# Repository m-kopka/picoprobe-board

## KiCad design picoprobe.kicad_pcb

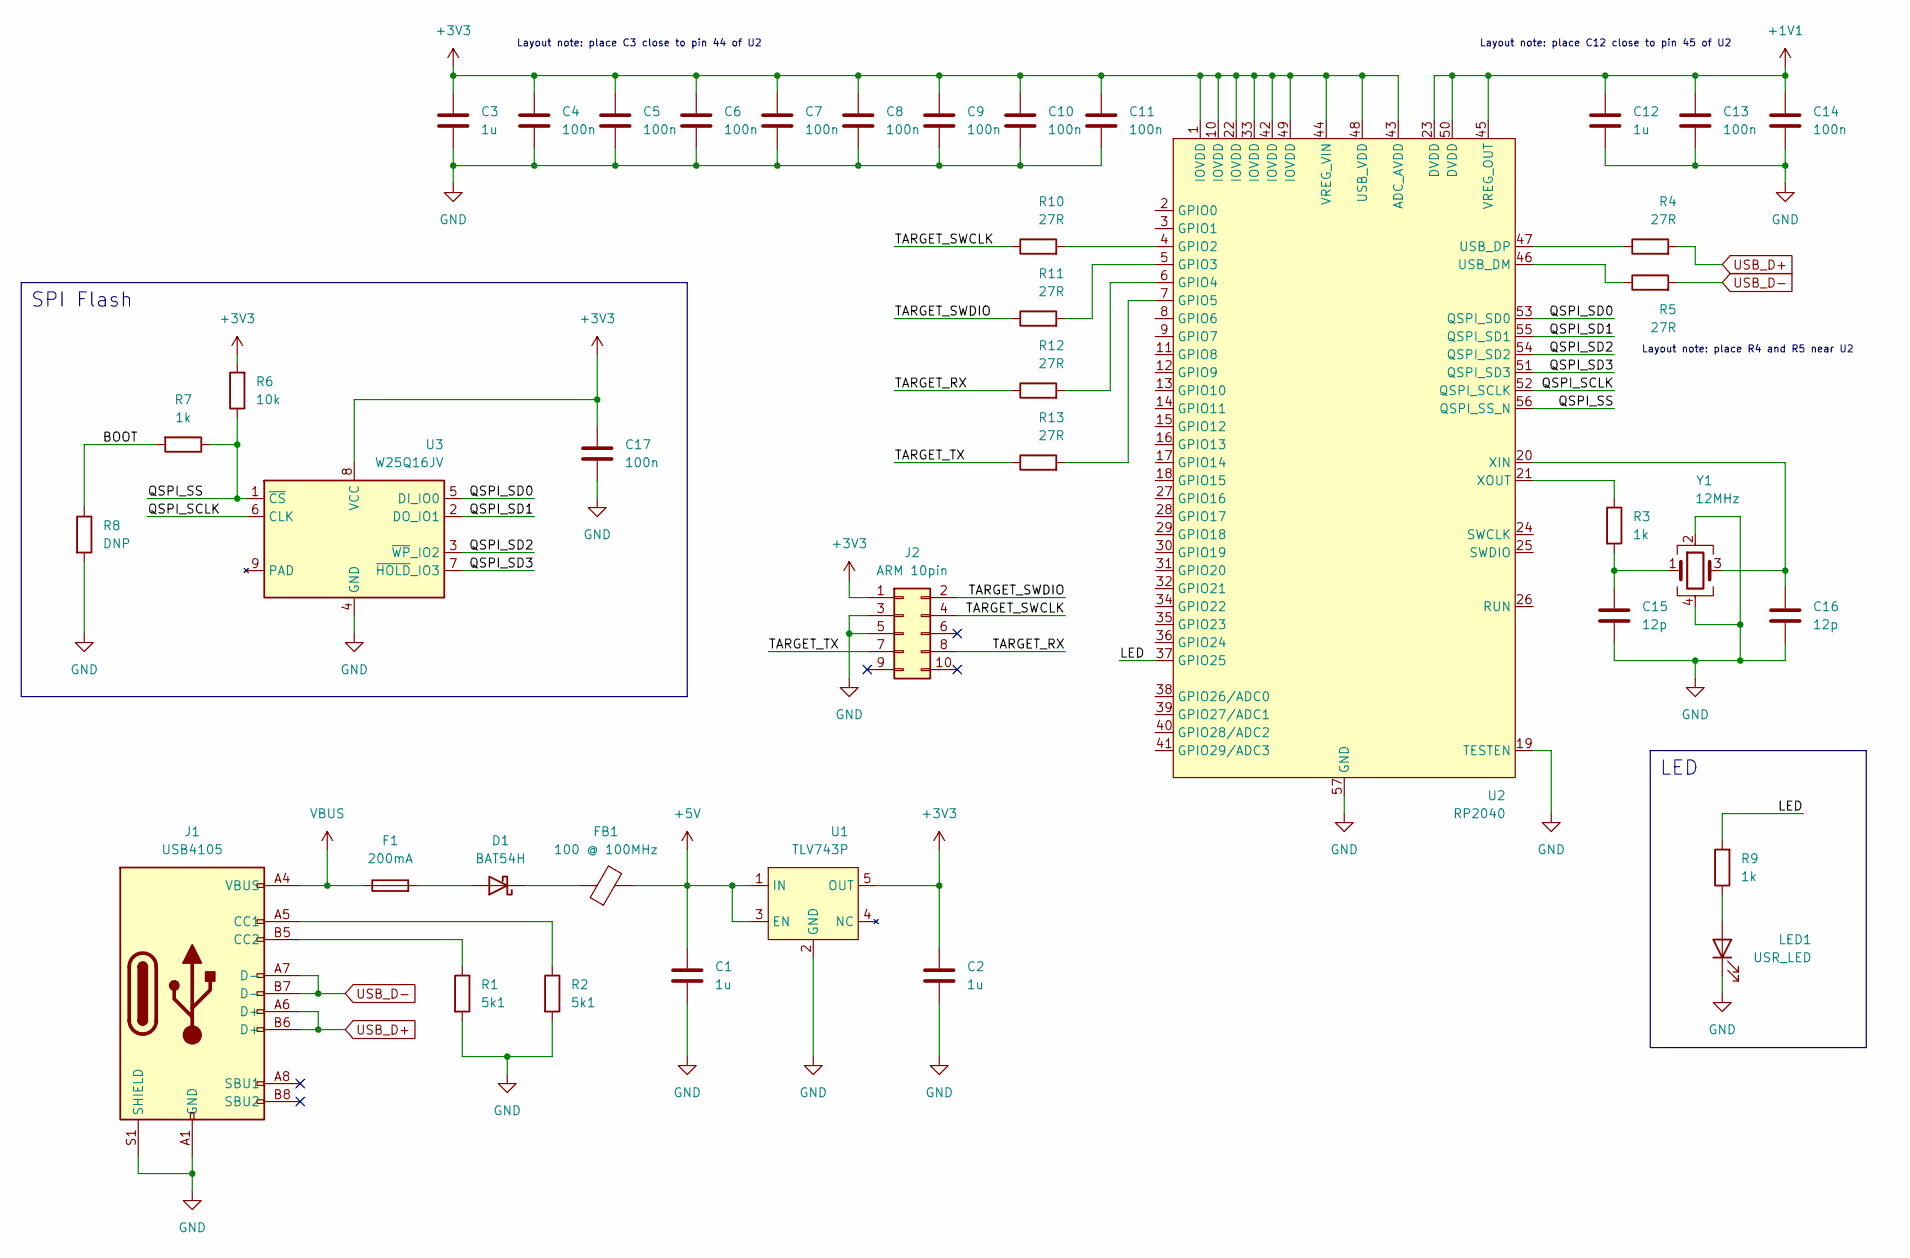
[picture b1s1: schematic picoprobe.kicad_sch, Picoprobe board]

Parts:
C1, C2, C3, C12: 1u; C_0402_1005Metric
C4, C5, C6, C7, C8, C9, C10, C11, C13, C14, C17: 100n; C_0402_1005Metric
C15, C16: 12p; C_0402_1005Metric
D1: BAT54H; SOD-123LF
F1: 200mA; R_0603_1608Metric
FB1: 100 @ 100MHz; R_0402_1005Metric
J1: USB4105
J2: ARM 10pin; MLW10 Edge
LED1: USR_LED; LED 0603
R1, R2: 5k1; R_0402_1005Metric
R3, R7, R9: 1k; R_0402_1005Metric
R4, R5, R10, R11, R12, R13: 27R; R_0402_1005Metric
R6: 10k; R_0402_1005Metric
R8: DNP; R_0402_1005Metric
U1: TLV743P; SOT-23-5L
U2: RP2040; QFN-56 7x7mm P0.4mm
U3: W25Q16JV; USON-8 2x3mm
Y1: 12MHz; Crystal 3225 3.2x2.5mm 4pin

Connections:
+1V1: C12.1, C13.1, C14.1, U2.23 (DVDD), U2.45 (VREG_OUT), U2.50 (DVDD)
+3V3: C2.1, C3.1, C4.1, C5.1, C6.1, C7.1, C8.1, C9.1, C10.1, C11.1, C17.1, J2.1, R6.2, U1.5 (OUT), U2.1 (IOVDD), U2.10 (IOVDD), U2.22 (IOVDD), U2.33 (IOVDD), U2.42 (IOVDD), U2.43 (ADC_AVDD), U2.44 (VREG_VIN), U2.48 (USB_VDD), U2.49 (IOVDD), U3.8 (VCC)
+5V: C1.1, FB1.2, U1.1 (IN), U1.3 (EN)
/BOOT: R7.2, R8.1
/LED: R9.2, U2.37 (GPIO25)
/QSPI_SCLK: U2.52 (QSPI_SCLK), U3.6 (CLK)
/QSPI_SD0: U2.53 (QSPI_SD0), U3.5 (DI_IO0)
/QSPI_SD1: U2.55 (QSPI_SD1), U3.2 (DO_IO1)
/QSPI_SD2: U2.54 (QSPI_SD2), U3.3 (~WP_IO2)
/QSPI_SD3: U2.51 (QSPI_SD3), U3.7 (~HOLD_IO3)
/QSPI_SS: R6.1, R7.1, U2.56 (QSPI_SS_N), U3.1 (~CS)
/TARGET_RX: J2.8, R12.1
/TARGET_SWCLK: J2.4, R10.1
/TARGET_SWDIO: J2.2, R11.1
/TARGET_TX: J2.7, R13.1
GND: C1.2, C2.2, C3.2, C4.2, C5.2, C6.2, C7.2, C8.2, C9.2, C10.2, C11.2, C12.2, C13.2, C14.2, C15.2, C16.2, C17.2, J1.A1 (GND), J1.A12 (GND), J1.B1 (GND), J1.B12 (GND), J1.S1 (SHIELD), J2.3, J2.5, LED1.1 (K), R1.2, R2.2, R8.2, U1.2 (GND), U2.19 (TESTEN), U2.57 (GND), U3.4 (GND), Y1.2, Y1.4
unnamed: C15.1, R3.2, Y1.1
unnamed: C16.1, U2.20 (XIN), Y1.3
unnamed: D1.1 (K), FB1.1
unnamed: D1.2 (A), F1.2
unnamed: J1.A5 (CC1), R2.1
unnamed: J1.B5 (CC2), R1.1
unnamed: LED1.2 (A), R9.1
unnamed: R3.1, U2.21 (XOUT)
unnamed: R4.1, U2.47 (USB_DP)
unnamed: R5.1, U2.46 (USB_DM)
unnamed: R10.2, U2.4 (GPIO2)
unnamed: R11.2, U2.5 (GPIO3)
unnamed: R12.2, U2.6 (GPIO4)
unnamed: R13.2, U2.7 (GPIO5)
USB_D+: J1.A6 (D+), J1.B6 (D+), R4.2
USB_D-: J1.A7 (D-), J1.B7 (D-), R5.2
VBUS: F1.1, J1.A4 (VBUS), J1.A9 (VBUS), J1.B4 (VBUS), J1.B9 (VBUS)

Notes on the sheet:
SPI Flash
Layout note: place R4 and R5 near U2
Layout note: place C3 close to pin 44 of U2
LED
Layout note: place C12 close to pin 45 of U2

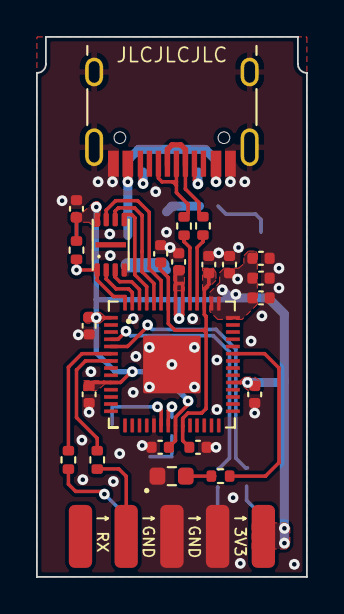
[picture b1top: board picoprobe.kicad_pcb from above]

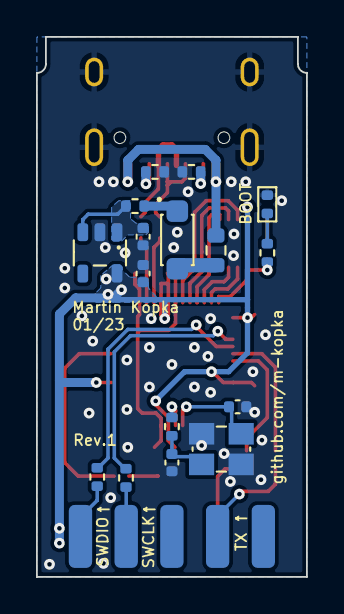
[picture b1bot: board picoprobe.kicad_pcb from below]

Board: 2 copper layers, 15.0 x 30.0 mm, 40 parts (16 on the bottom side), 33 nets.

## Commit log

2024-03-02 add: README.md
